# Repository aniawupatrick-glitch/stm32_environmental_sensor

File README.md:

# STM32 Environmental Monitoring PCB Design

## Overview

This project involved designing a printed circuit board (PCB) for an STM32-based environmental monitoring system during my internship at Zaptek. The system was intended to interface with environmental sensors and a display.

## Design Objectives

- Design a PCB for an STM32-based environmental monitoring system.
- Provide hardware connections for temperature, humidity and light sensors.
- Incorporate the required connections for a display.
- Organise components and connections into a practical PCB layout.

## My Contribution

My role focused on PCB design using **KiCad**. This repository will document the hardware design work I am authorised to share from the internship.

## Tools and Technologies

- **PCB Design Software:** KiCad
- **Microcontroller Platform:** STM32
- **Hardware:** Environmental sensors and display interface
- **Engineering Focus:** PCB layout and electronic hardware design

## Project Documentation

Where permission allows, this repository may include:

- PCB layout screenshots
- Schematic diagrams
- 3D PCB renders
- Gerber files or other manufacturing outputs

## Skills Demonstrated

- PCB design using KiCad
- Electronic component placement and board layout
- Hardware interfacing for microcontrollers and sensors
- Electronic design documentation

## Internship Context

This project was undertaken during my internship at Zaptek. Company-owned designs and confidential information will only be published with the appropriate permission.

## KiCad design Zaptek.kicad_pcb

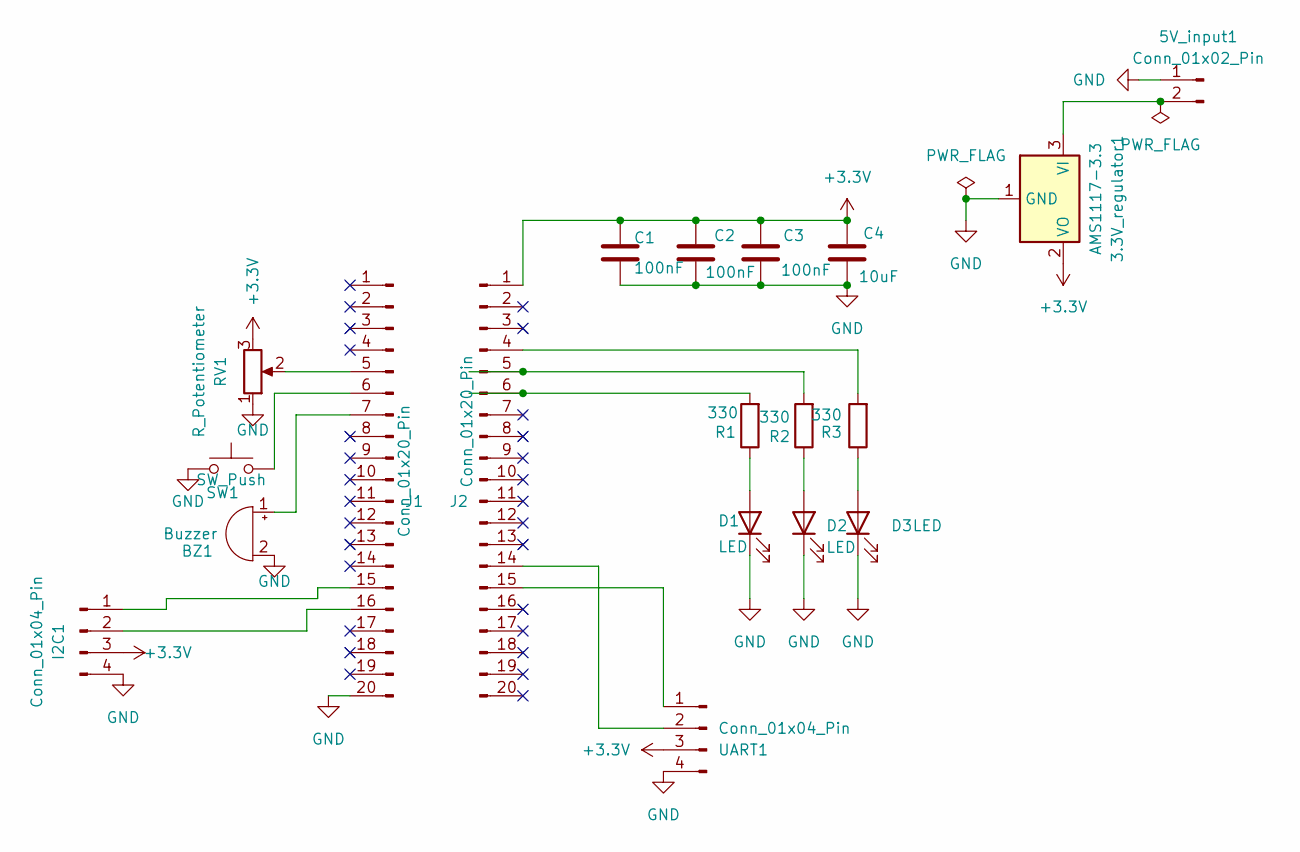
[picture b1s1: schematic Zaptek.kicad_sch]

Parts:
3.3V_regulator1: AMS1117-3.3; SOT-223-3_TabPin2
5V_input1: Conn_01x02_Pin; PinHeader_1x02_P2.54mm_Vertical
BZ1: Buzzer; Buzzer_12x9.5RM7.6
C1, C2, C3: 100nF; C_0805_2012Metric
C4: 10uF; C_0805_2012Metric
D1, D2, D3: LED; LED_0805_2012Metric
I2C1: Conn_01x04_Pin; PinSocket_1x04_P2.54mm_Vertical
J1, J2: Conn_01x20_Pin; PinSocket_1x20_P2.54mm_Vertical
R1, R2, R3: 330; R_0805_2012Metric
RV1: R_Potentiometer; Potentiometer_Bourns_3214W_Vertical
SW1: SW_Push; SW_Push_SPST_NO_Alps_SKRK
UART1: Conn_01x04_Pin; PinSocket_1x04_P2.54mm_Vertical

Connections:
+3.3V: 3.3V_regulator1.2 (VO), C1.1, C2.1, C3.1, C4.1, I2C1.3, J2.1, RV1.3, UART1.3
GND: 3.3V_regulator1.1 (GND), 5V_input1.1, BZ1.2 (-), C1.2, C2.2, C3.2, C4.2, D1.1 (K), D2.1 (K), D3.1 (K), I2C1.4, J1.20, RV1.1, SW1.2, UART1.4
unnamed: 3.3V_regulator1.3 (VI), 5V_input1.2
unnamed: BZ1.1 (+), J1.7
unnamed: D1.2 (A), R1.1
unnamed: D2.2 (A), R2.1
unnamed: D3.2 (A), R3.1
unnamed: I2C1.1, J1.15
unnamed: I2C1.2, J1.16
unnamed: J1.5, RV1.2
unnamed: J1.6, SW1.1
unnamed: J2.4, R3.2
unnamed: J2.5, R2.2
unnamed: J2.6, R1.2
unnamed: J2.14, UART1.2
unnamed: J2.15, UART1.1

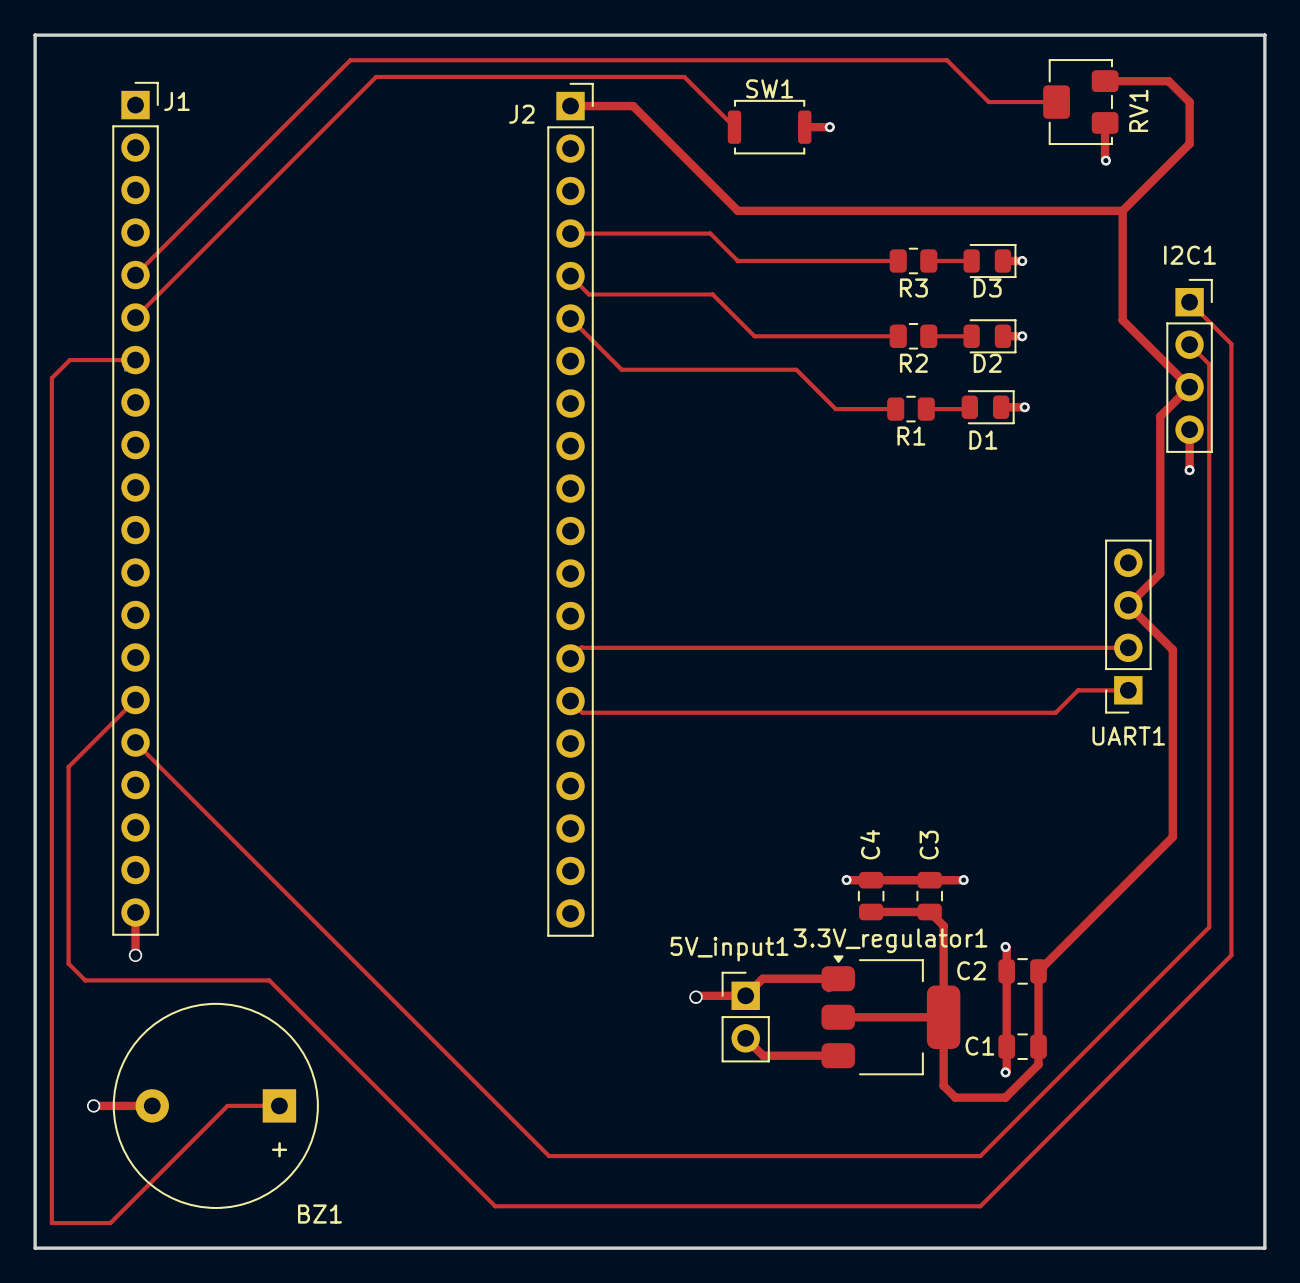
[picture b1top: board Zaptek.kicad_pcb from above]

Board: 2 copper layers, 73.5 x 72.5 mm, 19 parts (0 on the bottom side), 16 nets.

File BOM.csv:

"Id";"Designator";"Footprint";"Quantity";"Designation";"Supplier and ref";
1;"3.3V_regulator1";"SOT-223-3_TabPin2";1;"AMS1117-3.3";;;
2;"5V_input1";"PinHeader_1x02_P2.54mm_Vertical";1;"Conn_01x02_Pin";;;
3;"BZ1";"Buzzer_12x9.5RM7.6";1;"Buzzer";;;
4;"C1, C2, C3";"C_0805_2012Metric";3;"100nF";;;
5;"C4";"C_0805_2012Metric";1;"10uF";;;
6;"D1, D2, D3";"LED_0805_2012Metric";3;"LED";;;
7;"I2C1, UART1";"PinSocket_1x04_P2.54mm_Vertical";2;"Conn_01x04_Pin";;;
8;"J1, J2";"PinSocket_1x20_P2.54mm_Vertical";2;"Conn_01x20_Pin";;;
9;"R1, R2, R3";"R_0805_2012Metric";3;"330";;;
10;"RV1";"Potentiometer_Bourns_3214W_Vertical";1;"R_Potentiometer";;;
11;"SW1";"SW_Push_SPST_NO_Alps_SKRK";1;"SW_Push";;;
